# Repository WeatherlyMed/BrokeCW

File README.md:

# BrokeCW
A 40m Ham Radio Transeiver build intended to be cheaper than an pixie radio while allowing for change in frequency and includes a autokey for iambic CW keyers
## Schematic for Best design with autokey: https://github.com/WeatherlyMed/BrokeCW/blob/main/artifact/ButtonSchematic.pdf

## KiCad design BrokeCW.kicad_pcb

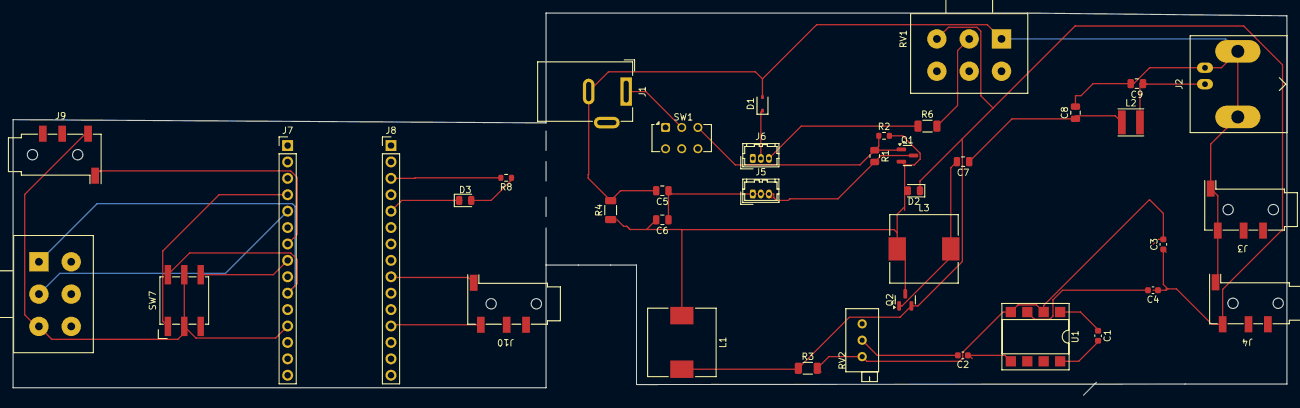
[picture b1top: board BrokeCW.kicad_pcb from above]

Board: 2 copper layers, 197.2 x 59.2 mm, 39 parts (0 on the bottom side), 27 nets.

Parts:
C1, C2: C 10uF; C_0603_1608Metric
C3, C4: C; C_0603_1608Metric
C5, C6: C100p; C_0805_2012Metric
C7: C0.01uF; C_0805_2012Metric
C8, C9: C_Small; C_0805_2012Metric
D1: D_C145491; D_SOD-323
D2, D3: LED; LED_0805_2012Metric
J1: Barrel_Jack_MountingPin; BarrelJack_Wuerth_6941xx301002
J2: Conn_Coaxial; BNC_Amphenol_B6252HB-NPP3G-50_Horizontal
J3, J4: AudioJack3_Ground; Jack_3.5mm_KoreanHropartsElec_PJ-320D-4A_Horizontal
J5, J6: Conn_01x03_Pin; Hirose_DF13-03P-1.25DSA_1x03_P1.25mm_Vertical
J7: Conn_01x15_PinLeft; PinHeader_1x15_P2.54mm_Vertical
J8: Conn_01x15_PinRight; PinHeader_1x15_P2.54mm_Vertical
J9: AudioJack3_Key; Jack_3.5mm_KoreanHropartsElec_PJ-320D-4A_Horizontal
J10: AudioJack3_Radio; Jack_3.5mm_KoreanHropartsElec_PJ-320D-4A_Horizontal
L1: L_100uH; L_10.4x10.4_H4.8
L2: 1uH; L_Taiyo-Yuden_MD-4040
L3: L; L_10.4x10.4_H4.8
Q1: 9013; SOT-23
Q2: 8050; SOT-23
R1: R47k; R_0805_2012Metric
R2: R33k; R_0603_1608Metric
R3: R10K; R_1206_3216Metric
R4: R; R_1206_3216Metric
R6: R100k; R_1206_3216Metric
R8: R; R_0603_1608Metric
RV1: R_Pot50k; Potentiometer_Alps_RK163_Dual_Horizontal
RV2: R_100ohm; Potentiometer_Bourns_3296X_Horizontal
RV3: R_Potentiometer_10k; Potentiometer_Alps_RK163_Dual_Horizontal
SW1: SW_DPDT_x2; SW_CK_JS202011CQN_DPDT_Straight
SW7: SW_Coded_SH-7050; Nidec_Copal_SH-7010B
U1: LM386; DIP-8_W7.62mm_SMDSocket_SmallPads

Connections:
unnamed: C1.1, U1.1 (GAIN)
unnamed: C1.2, U1.8 (GAIN)
unnamed: C2.1, U1.5
unnamed: C2.2, RV2.2
unnamed: C7.1, C8.1, L2.1
unnamed: C3.2, C5.2, C8.2, C9.2, D1.2 (A), J1.2, J2.2 (Ext), J3.S, J3.T, J4.S, R3.2, R4.2, RV1.1, RV2.3, U1.2 (-), U1.4 (GND)
unnamed: D1.1 (K), J6.1, J6.2, J6.3, R6.1
unnamed: C6.2, D2.2 (A), L1.1, L3.1, Q1.2 (E), Q2.3 (B), R2.2, R4.1
unnamed: C3.1, C4.1, D2.1 (K), J4.T, L1.2, Q2.2 (E), R3.1, RV1.3
unnamed: D3.2 (A), R8.1
unnamed: D3.1 (K), J8.5
unnamed: C9.1, J2.1 (In), L2.2
unnamed: C5.1, C6.1, J5.1, J5.2, J5.3, Q1.3 (B), R1.2
unnamed: J7.4, SW7.1
unnamed: J7.5, RV3.2
unnamed: J7.7, J9.S
unnamed: J7.8, SW7.2
unnamed: J7.10, RV3.1, SW7.8
unnamed: J7.12, J9.T, RV3.3, SW7.C
unnamed: J8.3, R8.2
unnamed: J8.9, J10.S
unnamed: J8.12, J10.T
unnamed: Q1.1 (C), R1.1, R2.1, SW1.3 (C)
unnamed: C7.2, L3.2, Q2.1 (C)
unnamed: R6.2, RV1.2
unnamed: J1.1, SW1.2 (B)
unnamed: C4.2, U1.3 (+)

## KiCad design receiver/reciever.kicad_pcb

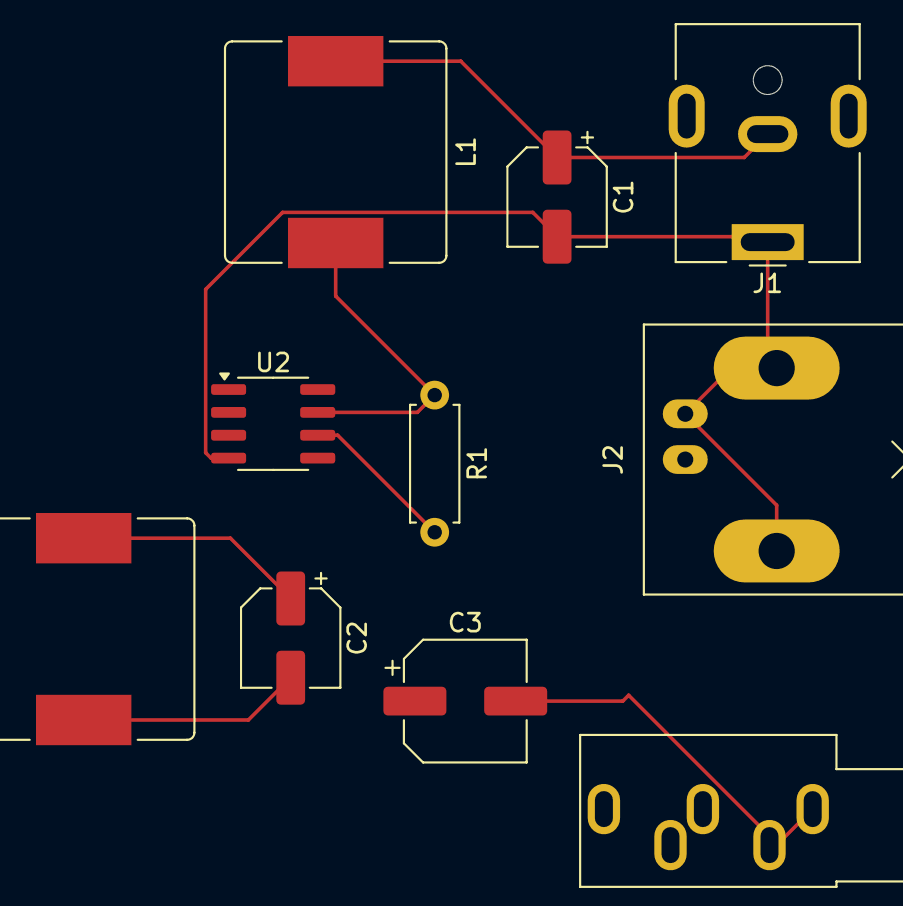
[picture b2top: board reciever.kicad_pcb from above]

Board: 2 copper layers, 10 parts (0 on the bottom side), 7 nets.

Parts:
C1, C2: C_Polarized_Small; CP_Elec_5x5.4
C3: C_Polarized_Small; CP_Elec_6.3x5.4
J1: Barrel_Jack_Switch; BarrelJack_CUI_PJ-063AH_Horizontal
J2: Conn_Coaxial_Power; BNC_Amphenol_B6252HB-NPP3G-50_Horizontal
J3: AudioJack2_Ground_Switch; Jack_3.5mm_CUI_SJ1-3535NG_Horizontal
L1, L2: L_Ferrite; L_Bourns_SRR1210A
R1: R_Small; R_Axial_DIN0207_L6.3mm_D2.5mm_P7.62mm_Horizontal
U2: LM741; SOIC-8_3.9x4.9mm_P1.27mm

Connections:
unnamed: C1.1, J1.2, L1.1
unnamed: C3.1, R1.2, U2.6
unnamed: C3.2, J3.S, J3.T
unnamed: C1.2, J1.1, J2.2 (Ext), U2.4 (V-)
unnamed: C2.1, J2.1 (In), L2.2
unnamed: C2.2, L2.1, U2.2 (-)
unnamed: L1.2, R1.1, U2.7 (V+)

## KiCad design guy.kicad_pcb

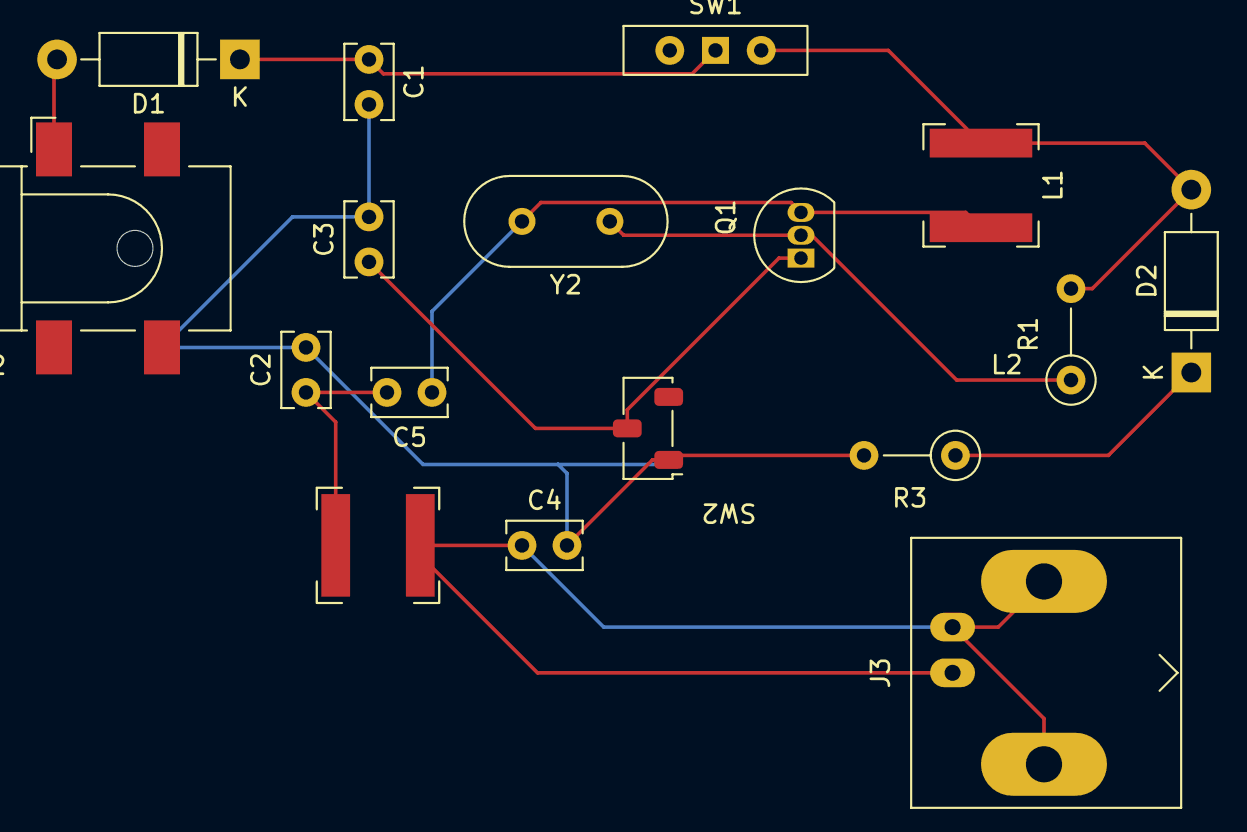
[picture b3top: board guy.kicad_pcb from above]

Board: 2 copper layers, 17 parts (0 on the bottom side), 11 nets.

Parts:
C1, C2, C3, C4, C5: C; C_Rect_L4.0mm_W2.5mm_P2.50mm
D1, D2: 1N4001; D_DO-41_SOD81_P10.16mm_Horizontal
J2: Barrel_Jack_MountingPin; BarrelJack_CLIFF_FC681465S_SMT_Horizontal
J3: Conn_Coaxial; BNC_Amphenol_B6252HB-NPP3G-50_Horizontal
L1, L2: L; L_Bourns-SRN6028
Q1: 2N3906; TO-92_Inline
R1, R3: R; R_Axial_DIN0207_L6.3mm_D2.5mm_P5.08mm_Vertical
SW1: SW_Wuerth_450301014042; SW_Slide-03_Wuerth-WS-SLTV_10x2.5x6.4_P2.54mm
SW2: SW_Nidec_CAS-120A1; Nidec_Copal_CAS-120A
Y2: Crystal; Crystal_HC49-U_Vertical

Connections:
unnamed: C2.1, C5.2, L2.1
unnamed: D1.2 (A), J2.1
unnamed: C1.1, D1.1 (K), SW1.1 (B)
unnamed: D2.2 (A), L1.2, R1.2, SW1.3 (A)
unnamed: D2.1 (K), R3.1
unnamed: C4.1, J3.2 (Ext)
unnamed: J3.1 (In), L2.2
unnamed: Q1.2 (B), R1.1, Y2.1
unnamed: C5.1, L1.1, Q1.3 (C), Y2.2
unnamed: C3.1, Q1.1 (E), SW2.2 (B)
unnamed: C1.2, C2.2, C3.2, C4.2, J2.2, R3.2, SW2.1 (C)

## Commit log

2024-07-25 Radio Out Circuit Notes
2024-07-25 Update design to use variable crystal
2024-07-26 Update to circuit with my current materials
2024-07-26 Ignore BOM will fix in morning
2024-07-26 current assembly
2024-08-01 Rename IMG_20240726_001242909.jpg to artifact/IMG_20240726_001242909.jpg
2024-08-01 organise directory
2024-08-09 Create antenna test
2024-08-09 Update antenna test
2024-08-10 Create text
2024-08-23 reorganised the files
